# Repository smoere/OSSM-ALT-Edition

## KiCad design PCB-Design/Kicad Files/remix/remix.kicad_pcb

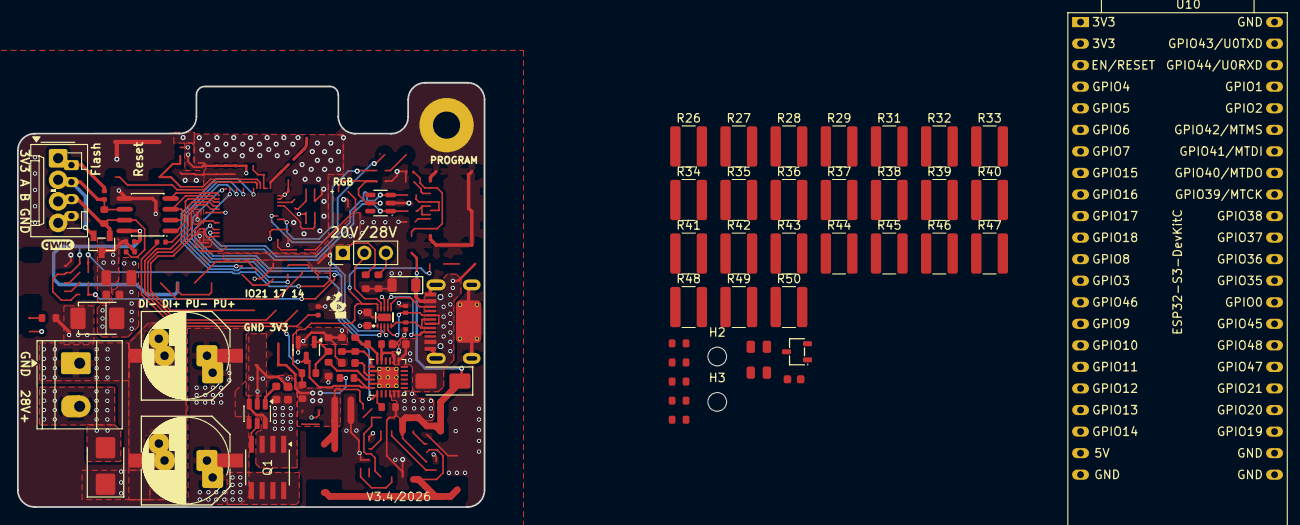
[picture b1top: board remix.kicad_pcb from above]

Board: 4 copper layers, 55.0 x 50.0 mm, 84 parts (0 on the bottom side), 45 nets.

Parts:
C1, C3: 1uF; C_0603
C2: 100nF; C_0402
C4, C5, C6, C13, C16: 100nF; C_0603
C7, C8: 680uF; CAP-SMD_BD10.0-L10.3-W10.3-LS11.3-FD
C9: 1nF; C_0402
C10, C11: 470uF; CP_Radial_D10.0mm_P5.00mm_P7.50mm
C12: 10uF; C_1206
C14, C15: 10uF; C_0805
D1: SMF30A; D_SOD-123FL
D2, D3: H5VL10BC; D_DFN1006-2L
D4: SS34; D_SMA
D7: SRV05-4; SOT-23-6_L2.9-W1.6-P0.95-LS2.8-BL-1
D8: SMBJ33CA; D_SMB
D9: ES5JBF; D_SMBF
H1: MountingHole_Pad; MountingHole_3.2mm_M3_Pad
H2, H3: MountingHole; MountingHole_2.2mm_M2_ISO14580
J1: Connector, USB-TYPE-C-16P; TYPE-C-SMD_HX-TYPE-C-16PIN
J3: RS485 con; OSSM ALT RS485 Connector
J4: power_con; TerminalBlock_Phoenix_MKDS-1,5-2-5.08_1x02_P5.08mm_Horizont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
JP1: Jumper_3_Open; PinHeader_1x03_P2.54mm_Vertical
Q1: FDS5351; SO-8 N-channel mosfet FDS5351
Q2: BC817-25; Q_SOT-23
R1: 210kΩ; R_0603
R2, R23: 120kΩ; R_0603
R8: 120Ω; R_0603
R9, R10: 4.7kΩ; R_0402
R11, R18: 470kΩ; R_0603
R12: 13kΩ; R_0603
R13, R16, R21: 20kΩ; R_0603
R14: 3.3kΩ; R_0603
R15: 1.5kΩ; R_0402
R17, R20, R22: 10kΩ; R_0603
R19, R24: 47kΩ; R_0603
R25: 1MΩ; R_0603
R26, R27, R28, R29, R31, R32, R33, R34, R35, R36, R37, R38, R39, R40, R41, R42, R43, R44, R45, R46, R47, R48, R49, R50: 4.7Ω; R_1218_3246Metric_Pad1.22x4.75mm_HandSolder
R30: 10Ω; R_0603
U2: CH224Q; SON-10_L2.0-W2.0-P0.40-TL-EP
U3: SP3485EN; SOIC-8_L5.0-W4.0-P1.27-LS6.0-BL
U4: SM712-02HTG; SOT-23-3_L2.9-W1.3-P1.90-LS2.4-BR
U5: TPS16630RGER; VQFN-24-1EP_4x4mm_P0.5mm_EP2.5x2.5mm_ThermalVias
U6: LM74700; SOT-23-6
U8: CJ431; SOT-23-3_L2.9-W1.6-P1.90-LS2.8-BR
U10: ESP32-S3-DevKitC

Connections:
+3V3: C2.1, D7.5 (VP), J3.1, R10.2, R17.1, R20.1, U3.8 (VCC), U10.1 (3V3), U10.2 (3V3)
+12V: C15.2, C16.1, R24.2
+28V: C4.1, C5.1, Q1.2 (S), U5.17 (OUT), U5.18 (OUT), U6.3 (EN), U6.6 (ANODE)
/A: J3.2, R8.2, R10.1, U3.6 (A), U4.2
/B: J3.3, R8.1, R9.2, U3.7 (B), U4.1
/CC1: J1.A5 (CC1), U2.7 (CC1)
/CC2: J1.B5 (CC2), U2.6 (CC2)
/CSENSE: R16.1, U5.13 (IMON), U10.6 (GPIO6/ADC1_CH5)
/DI: U3.4 (DI), U10.16 (GPIO10/ADC1_CH9)
/D_N2: D2.2, J1.A7 (D-), J1.B7 (D-), U2.5 (DM)
/D_P2: D3.2, J1.A6 (D+), J1.B6 (D+), U2.4 (DP)
/Motor_Power/V_MOT: C7.1, C8.1, C10.1, C11.1, C12.1, C13.1, D8.2, D9.1, J4.2, Q1.3 (D), R21.1, U6.4 (CATHODE)
/PG: R19.2, R20.2, U2.10 (PG)
/RE/DE: U3.2 (RE#), U3.3 (DE), U10.17 (GPIO11/ADC2_CH0)
/RO: U3.1 (RO), U10.18 (GPIO12/ADC2_CH1)
/SCL: U2.2 (CFG2/SCL), U10.15 (GPIO9/ADC1_CH8)
/SDA: U2.3 (CFG3/SDA), U10.12 (GPIO8/ADC1_CH7)
/SHDN: R15.1, U10.19 (GPIO13/ADC2_CH2)
GND: C1.2, C2.2, C3.2, C4.2, C6.2, C7.2, C8.2, C9.2, C10.2, C11.2, C12.2, C13.2, C14.1, C15.1, C16.2, D1.2, D2.1, D3.1, D7.2 (VN), D8.1, D9.2, H1.1 (1_1), J1.A12B1 (GND), J1.B12A1 (GND), J1.S1 (SHIELD), J3.4, J4.1, Q2.2 (E), R1.1, R2.1, R9.1, R13.2, R14.2, R16.2, R18.2, R21.2, R22.1, U2.11 (EP), U3.5 (GND), U4.3, U5.8 (GND), U5.11 (MODE), U5.25 (GND), U6.2 (GND), U8.3 (AN), U10.22 (GND), U10.23 (GND), U10.24 (GND), U10.44 (GND)
unnamed: JP1.1 (A), R2.2
unnamed: JP1.3 (B), R1.2
unnamed: JP1.2 (C), U2.9 (CFG1)
unnamed: Q1.1 (G), U6.5 (GATE)
unnamed: Q2.1 (B), R18.1, R19.1
unnamed: C9.1, Q2.3 (C), R15.2, R17.2, U5.12 (~SHDN)
unnamed: R29.2, R34.2, R38.2, R42.2, R46.2, R50.2
unnamed: R26.2, R27.1, R31.2, R32.1
unnamed: R27.2, R28.1, R32.2, R33.1
unnamed: R28.2, R29.1, R33.2, R34.1
unnamed: R35.2, R36.1, R39.2, R40.1
unnamed: R36.2, R37.1, R40.2, R41.1
unnamed: R37.2, R38.1, R41.2, R42.1
unnamed: R43.2, R44.1, R47.2, R48.1
unnamed: R44.2, R45.1, R48.2, R49.1
unnamed: R45.2, R46.1, R49.2, R50.1
unnamed: R14.1, U5.10 (ILIM)
unnamed: R12.2, R13.1, U5.7 (OVP)
unnamed: R11.2, R12.1, U5.6 (UVLO)
unnamed: C6.1, U5.9 (dVdT)
unnamed: C5.2, U6.1 (VCAP)
unnamed: R24.1, U8.2 (CAT)
unnamed: R22.2, R23.2, R25.2, U8.1 (REF)
unnamed: R25.1, R30.1
VBUS: C1.1, C3.1, D1.1, D4.2, J1.A9B4 (VBUS), J1.B9A4 (VBUS), R11.1, U2.1 (VHV), U2.8 (VBUS), U5.1 (IN), U5.2 (IN), U5.5 (P_IN)
V_MOT: C14.2, R23.1, R26.1, R31.1, R35.1, R39.1, R43.1, R47.1
